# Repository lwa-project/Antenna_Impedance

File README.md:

Antenna_Impedance
===================

Description
-----------
Collection of scripts and files dealing with the LWA antenna impedance.

In the main directory are the general scripts:
* compute_IME.py: Reads in a single .s1p file containing antenna reflection coefficient data and computes the IME 
* plot_IME.py: Plots the output from computeIME.py along with the model IME from antenna simulations
* compute_IMF.py: Reads in a .npz file output by read_FEE_S_params.py and a collection of antenna .s2p files to compute the Impedance Mismatch Factor (IMF)
* plot_S_params.py: Takes in a collection of .s2p files and plots the full set of S-parameters for each antenna. Used to make the dipole-dipole measurement plots.
* plot_cross_coupling.py: Takes in a collection of .s2p files from an antenna-antenna cross coupling measurement and plots S12 and S21 for each of the four possible polarization permutations. 

Data Files
----------
In the Data/ directory there is a collection of various data files with their associated documentation.
Files include:
* BurnsZ.txt: Model IME from old antenna simulations
* A-NS_AntennaImpedance_062222.s1p: Antenna Impedance for A (N/S) polarization taken on 06/22/2022 at Whitham Reeve's house in Alaska
* B-EW_AntennaImpedance_062222.s1p: Antenna Impedance for B (E/W) polarization taken on 06/22/2022 at Whitham Reeve's house in Alaska
* A collection of dipole-dipole and antenna-antenna .s2p measurement files taken at the New Mexico stations (See "LWA_NM_Measurements_and_Procedures.pdf" for more information)

FEE
---
The Data/FEE/ directory contains:
* A collection of .s2p files which contains S-parameter measurements with the HX62A of the FEE Test Fixture de-embedded.
* read_FEE_S_params.py: A script to read both the .s1p and .s2p files and write out proper S-pramaters (S11 with HX62A de-embdedd, correct S21 and S12, and S22).
* plot_FEE_Gain.py: A script to plot the FEE Gain files which are output by read_FEE_S_params.py

Example
-------
The following is a short example which shows how to generate the IMF correction for LWA data, which requires both LWA antenna S11 measurements and FEE S11 measurements.
The FEE S11 data with the HX62A de-embedded are located in `Data/FEE/S1P/`. The single antenna measurements for each station are located in the named directories in the `Data/` directory
under `Dipole-Dipole/` (e.g. the LWA-SV measurements are in `Data/LWA-SV/Dipole-Dipole/`.

First, the FEE S-parameters with the HX62A de-embedded have to be collected into a single .npz file. To do this, use `Data/FEE/read_FEE_S_params.py` for both polarizations:
```
python3 read_FEE_S_params.py -ns S2P/*A*
```
and
```
python3 read_FEE_S_params.py -ns S2P/*B*
```
This creates two files `FEE_S11_NS.npz` and `FEE_S11_EW.npz`, respectively. Finally, to compute the IMF correction using LWA1 antenna measurements and FEE S11 measurements use `compute_IMF.py`
for each polarization via
```
python3 compute_IMF.py -ns Data/FEE/FEE_S11_NS.npz Data/LWA1/Dipole-Dipole/*
```
and
```
python3 compute_IMF.py -ns Data/FEE/FEE_S11_EW.npz Data/LWA1/Dipole-Dipole/*
```
This creates two files named `IMF_NS.txt` and `IMF_EW.txt`, respectively, which contain the IMF as a function of frequency along with the $16^{th}$ and $84^{th}$ percentile uncertainty bounds.

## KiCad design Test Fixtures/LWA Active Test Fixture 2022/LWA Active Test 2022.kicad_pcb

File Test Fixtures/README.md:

Test Fixtures
=============

Description
-----------
This directory contains the KiCAD v7 project files needed to build the test
fixtures used in [DiLullo et al. (2023, PASP)](https://arxiv.org/abs/2303.14904).
There are two sub-directories: "LWA Active Test Fixture 2022" and "LWA Cal Test
Fixture 2022".  "Active" contains the board that was used to make the impedance
measurements.  "Cal" contains the base board for making the open,
short, and load calibration fixtures for the measurements.

Within each sub-directory is the full KiCAD v7 project, the Gerber files, and BoM
for the board, relevant data sheets for the parts used, and an image of the
rendered 3D model of the full board.

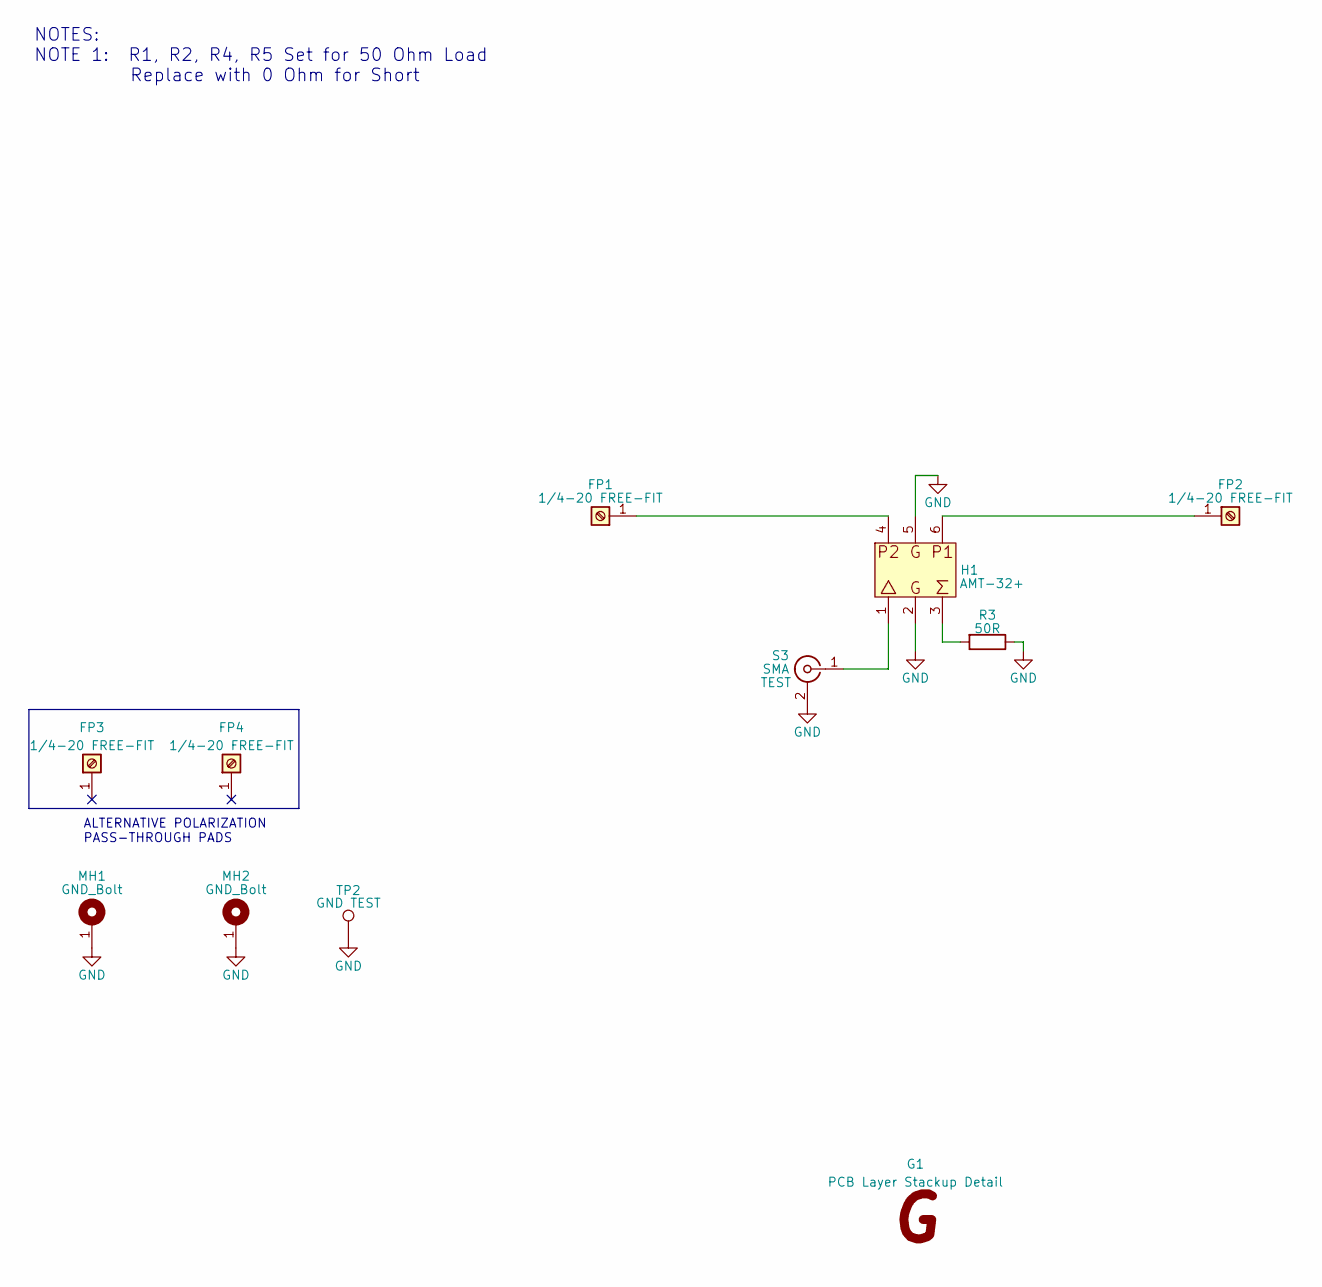
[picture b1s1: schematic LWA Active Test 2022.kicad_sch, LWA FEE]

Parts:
FP1, FP2, FP3, FP4: 1/4-20 FREE-FIT; Feedpoint; Tolerance NA; Voltage Rating NA; MPN DNI
G1: PCB Layer Stackup Detail; FabDrawing-2Layer-Imperial_LWA
H1: AMT-32+; AMT-2; Tolerance NA; Voltage Rating NA; MPN AMT-32+
MH1, MH2: GND_Bolt
R3: 50R; R_1206_3216Metric_Pad1.30x1.75mm_HandSolder; Tolerance 0.1%; Voltage Rating NA; MPN Y162550R0000B9W
S3: TEST; SMA_142-0701-201; Tolerance NA; Voltage Rating NA; MPN 142-0701-201
TP2: GND TEST; Harwin_TP_S1751-46R; Tolerance NA; Voltage Rating NA; MPN S1751-46R

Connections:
GND: H1.2, H1.5, MH1.1, MH2.1, R3.1, S3.2 (Ext), TP2.1
unnamed: FP1.1, H1.4
unnamed: H1.1, S3.1 (In)
unnamed: H1.3, R3.2
unnamed: FP2.1, H1.6

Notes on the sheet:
NOTES: NOTE 1: R1, R2, R4, R5 Set for 50 Ohm Load Replace with 0 Ohm for Short
ALTERNATIVE POLARIZATION PASS-THROUGH PADS

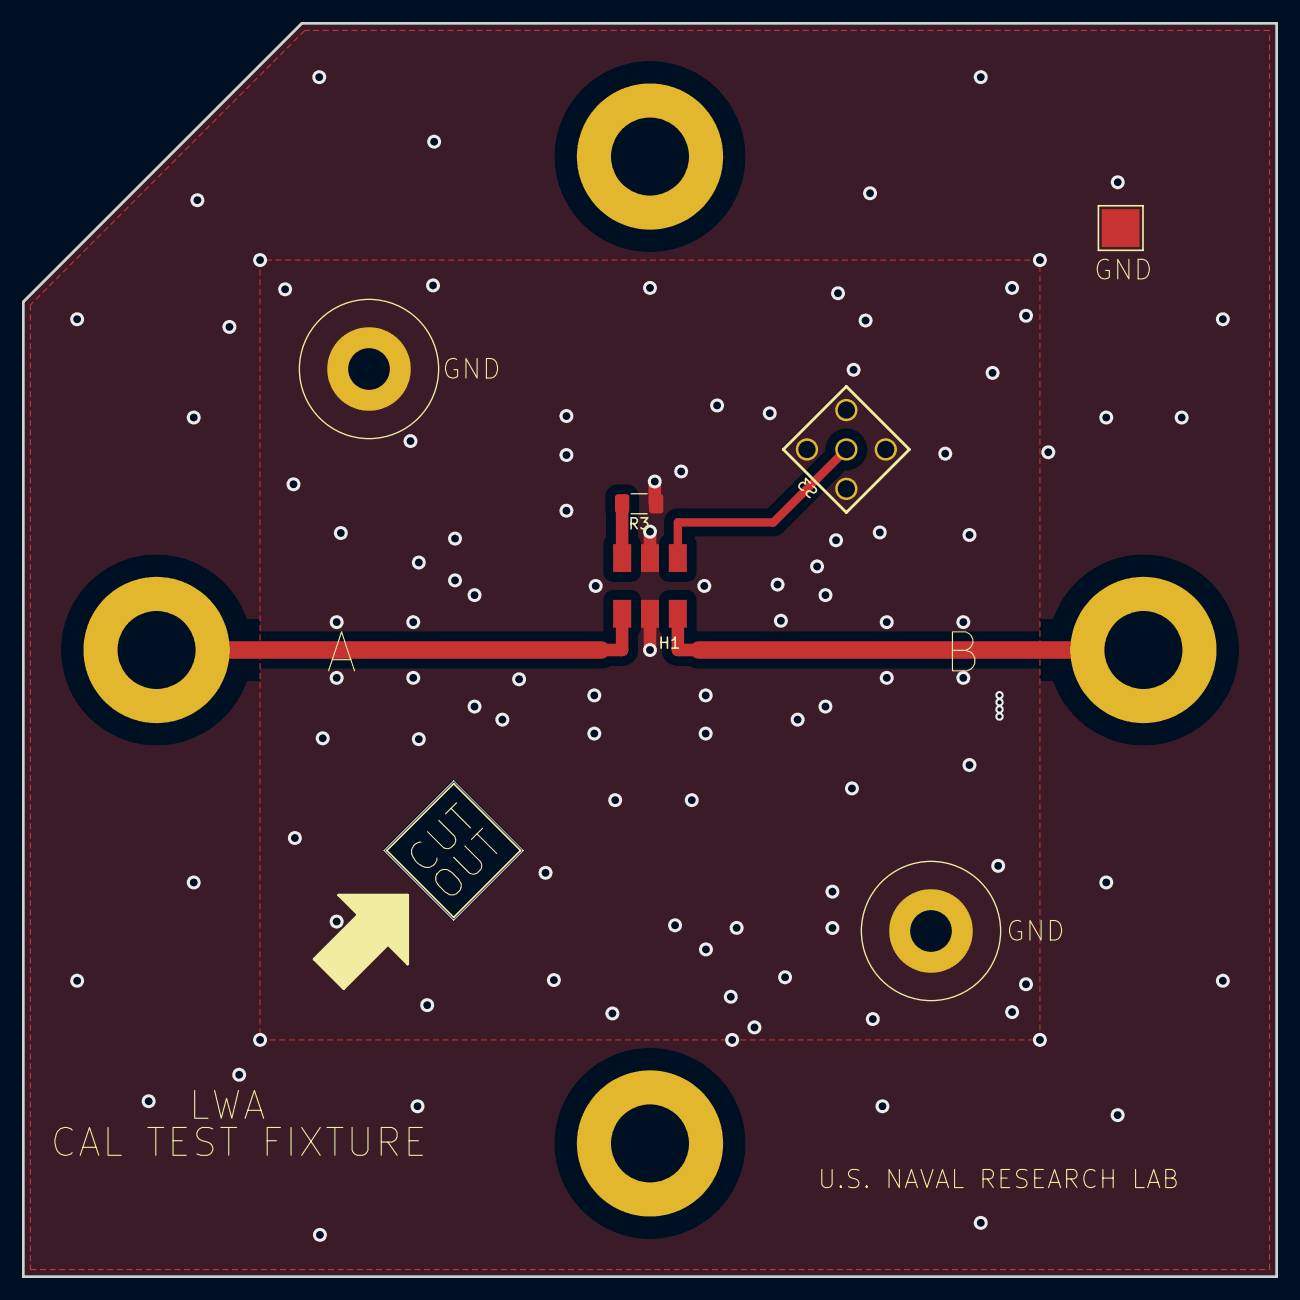
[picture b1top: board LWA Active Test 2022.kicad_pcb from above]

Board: 2 copper layers, 114.3 x 114.3 mm, 11 parts (1 on the bottom side), 5 nets.

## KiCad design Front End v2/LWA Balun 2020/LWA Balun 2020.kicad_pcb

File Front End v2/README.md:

LWA Front End Electronics (FEE) v2
==================================

Description
-----------
This directory contains the KiCAD v7 project files needed to build version 2 of
the LWA Front End Electronics board.  Inside "LWA Balun 2020" is the full KiCAD
v7 project, the Gerber files, and BoM for the board, relevant data sheets for
the parts used, and an image of the rendered 3D model of the full board.

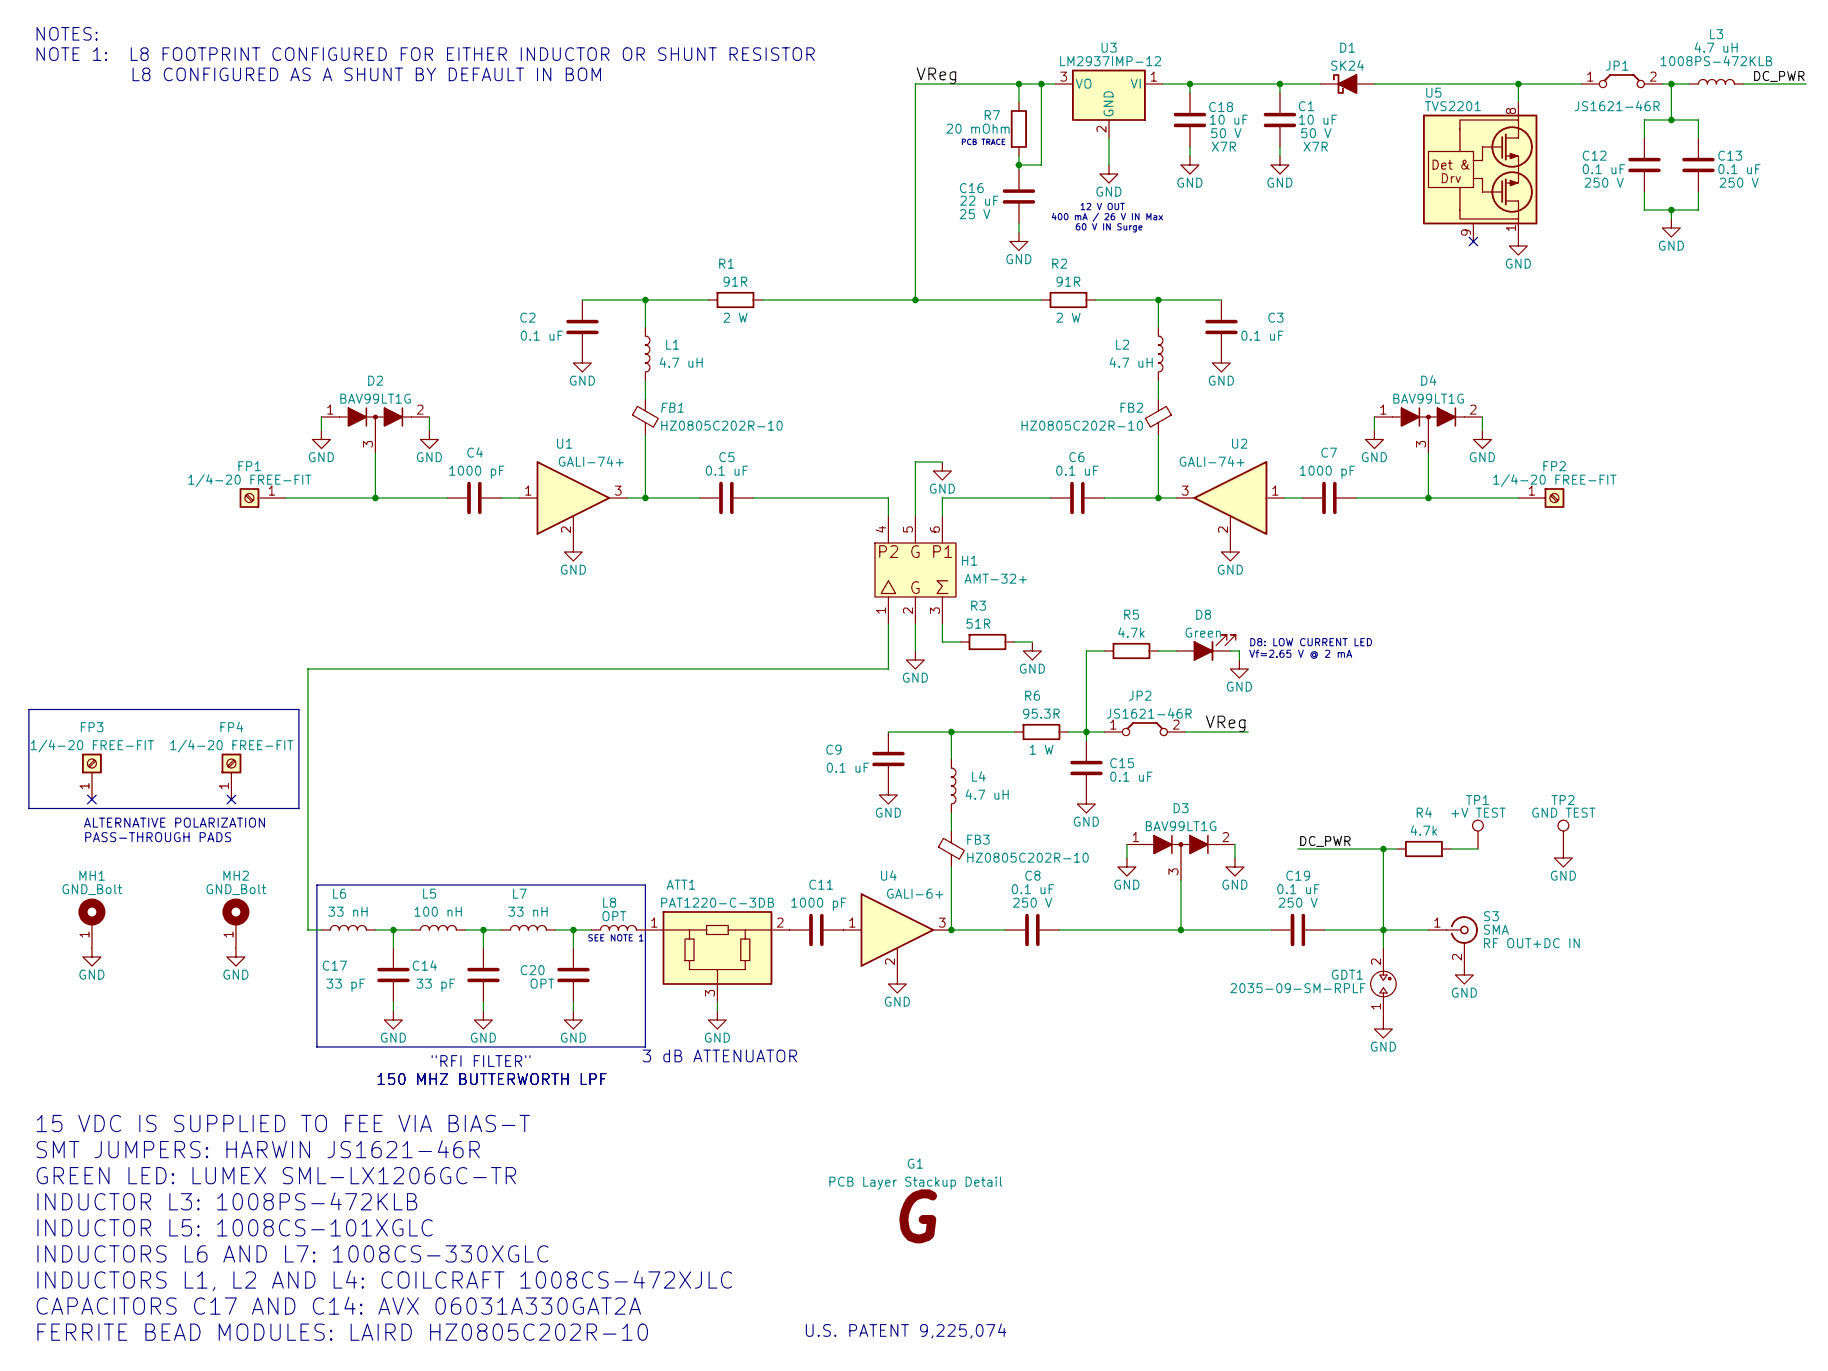
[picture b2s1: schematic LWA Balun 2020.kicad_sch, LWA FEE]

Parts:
ATT1: PAT1220-C-3DB; RF_Attenuator_Susumu_PAT1220_3D; Tolerance NA; Voltage Rating NA; MPN PAT1220-C-3DB-T5
C1, C18: 10 uF; C_1210_3225Metric_Pad1.33x2.70mm_HandSolder; Tolerance 10%; Voltage Rating 50 V; MPN CL32B106KBJNNWE
C2, C3, C5, C6, C8, C9, C12, C13, C15, C19: 0.1 uF; C_1206_3216Metric_Pad1.6x1.8mm; Tolerance 10%; Voltage Rating 250 V; MPN CC1206KKX7RYBB104
C4, C7, C11: 1000 pF; C_1206_3216Metric_Pad1.6x1.8mm; Tolerance 10%; Voltage Rating 630 V; MPN C1206C102KBRACTU
C14, C17: 33 pF; C_0603_1608Metric_Pad1.08x0.95mm_HandSolder; Tolerance 2%; Voltage Rating 100 V; MPN 06031A330GAT2A
C16: 22 uF; C_1210_3225Metric_Pad1.33x2.70mm_HandSolder; Tolerance 10%; Voltage Rating 25 V; MPN GRM32ER71E226ME15K
C20: OPT; C_0603_1608Metric_Pad1.08x0.95mm_HandSolder; Tolerance 2%; Voltage Rating 100 V; MPN DNI
D1: SK24; D_SMB_Handsoldering; Tolerance NA; Voltage Rating 500 mV @ 2 A; MPN SK24
D2, D3, D4: BAV99LT1G; SOT-23; Rating (A) 215 mA; Tolerance NA; MPN BAV99LT1G
D8: Green; LED_1206_3216Metric; Tolerance NA; Voltage Rating 2.65 V; MPN APT3216LZGCK
FB1, FB2, FB3: HZ0805C202R-10; L_0805_2012Metric_Pad1.15x1.40mm_HandSolder; Tolerance NA; Voltage Rating NA; MPN HZ0805C202R-10
FP1, FP2, FP3, FP4: 1/4-20 FREE-FIT; Feedpoint; Tolerance NA; Voltage Rating NA; MPN DNI
G1: PCB Layer Stackup Detail; FabDrawing-2Layer-Imperial_LWA
GDT1: 2035-09-SM-RPLF; Tolerance NA; Voltage Rating 90 V; MPN 2035-09-SM-RPLF
H1: AMT-32+; AMT-2; Tolerance NA; Voltage Rating NA; MPN AMT-32+
JP1, JP2: JS1621-46R; S1621-46R; Tolerance NA; Voltage Rating NA; MPN S1621-46R
L1, L2, L4: 4.7 uH; 1008CS; Tolerance 5%; Voltage Rating NA; MPN 1008CS-472XJLC
L3: 4.7 uH; 1008PS; Tolerance 10%; Voltage Rating NA; MPN 1008PS-472KLB
L5: 100 nH; 1008CS; Tolerance 2%; Voltage Rating NA; MPN 1008CS-101XGLC
L6, L7: 33 nH; 1008CS; Tolerance 2%; Voltage Rating NA; MPN 1008CS-330XGLC
L8: OPT; 1008CS_RES; Tolerance 2%; Voltage Rating NA; MPN RMCF0603ZT0R00
MH1, MH2: GND_Bolt
R1: 91R; R_2512_6332Metric_Pad1.8x3.35mm; Tolerance 1%; Voltage Rating NA; MPN 352191RFT
R2: 91R; R_2512_6332Metric_Pad1.8x3.35mm; Tolerance 1%; Voltage Rating 200 V; MPN 352191RFT
R3: 51R; R_1206_3216Metric_Pad1.30x1.75mm_HandSolder; Tolerance 1%; Voltage Rating NA; MPN RMCF1206FT51R0
R4, R5: 4.7k; R_1206_3216Metric_Pad1.30x1.75mm_HandSolder; Tolerance 5%; Voltage Rating NA; MPN ERJ-8GEYJ472V
R6: 95.3R; R_2512_6332Metric_Pad1.8x3.35mm; Tolerance 1%; Voltage Rating NA; MPN RMCF2512FT95R3
R7: 20 mOhm; ESR_20_mOhm; Tolerance NA; Voltage Rating NA; MPN Virtual
S3: RF OUT+DC IN; SMA_142-0701-201; Tolerance NA; Voltage Rating NA; MPN 142-0701-201
TP1: +V TEST; Harwin_TP_S1751-46R; Tolerance NA; Voltage Rating NA; MPN S1751-46R
TP2: GND TEST; Harwin_TP_S1751-46R; Tolerance NA; Voltage Rating NA; MPN S1751-46R
U1, U2: GALI-74+; MCL_Gali; Tolerance NA; Voltage Rating NA; MPN GALI-74+
U3: LM2937IMP-12; SOT-223-3_TabPin2; Tolerance NA; Voltage Rating NA; MPN LM2937IMP-12/NOPB
U4: GALI-6+; MCL_Gali; Tolerance NA; Voltage Rating NA; MPN GALI-6+
U5: TVS2201; Texas_DRB0008A_VSON-N8_No_Vias; Tolerance NA; Voltage Rating Standoff ±22 V / Clamping 29.6 V; MPN TVS2201DRBR

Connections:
/DC_PWR: C19.1, GDT1.2, L3.1, R4.1, S3.1 (In)
/VReg: C16.2, JP2.2 (B), R1.1, R2.1, R7.1, R7.2, U3.3 (VO)
GND: ATT1.3, C1.1, C2.1, C3.1, C9.1, C12.1, C13.1, C14.1, C15.1, C16.1, C17.1, C18.1, C20.1, D2.1 (K), D2.2 (A), D3.1 (K), D3.2 (A), D4.1 (K), D4.2 (A), D8.1 (K), GDT1.1, H1.2, H1.5, MH1.1, MH2.1, R3.1, S3.2 (Ext), TP2.1, U1.2, U2.2, U3.2 (GND), U4.2, U5.1 (GND), U5.2 (GND), U5.3 (GND), U5.4 (GND)
unnamed: ATT1.1, L8.2
unnamed: ATT1.2, C11.2
unnamed: C2.2, L1.1, R1.2
unnamed: C3.2, L2.1, R2.2
unnamed: C4.1, U1.1
unnamed: C5.1, H1.4
unnamed: C5.2, FB1.2, U1.3
unnamed: C6.1, H1.6
unnamed: C6.2, FB2.2, U2.3
unnamed: C7.1, U2.1
unnamed: C8.2, FB3.2, U4.3
unnamed: C9.2, L4.1, R6.2
unnamed: C11.1, U4.1
unnamed: C14.2, L5.2, L7.1
unnamed: C17.2, L5.1, L6.2
unnamed: C8.1, C19.2, D3.3 (K)
unnamed: C20.2, L7.2, L8.1
unnamed: D1.2 (A), JP1.1 (A), U5.5 (IN), U5.6 (IN), U5.7 (IN), U5.8 (IN)
unnamed: C1.2, C18.2, D1.1 (K), U3.1 (VI)
unnamed: D8.2 (A), R5.2
unnamed: FB1.1, L1.2
unnamed: FB2.1, L2.2
unnamed: FB3.1, L4.2
unnamed: C4.2, D2.3 (K), FP1.1
unnamed: C7.2, D4.3 (K), FP2.1
unnamed: H1.1, L6.1
unnamed: H1.3, R3.2
unnamed: C12.2, C13.2, JP1.2 (B), L3.2
unnamed: C15.2, JP2.1 (A), R5.1, R6.1
unnamed: R4.2, TP1.1

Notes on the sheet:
PCB TRACE
"RFI FILTER"
U.S. PATENT 9,225,074
150 MHZ BUTTERWORTH LPF
D8: LOW CURRENT LED Vf=2.65 V @ 2 mA
NOTES: NOTE 1: L8 FOOTPRINT CONFIGURED FOR EITHER INDUCTOR OR SHUNT RESISTOR L8 CONFIGURED AS A SHUNT BY DEFAULT IN BOM
SEE NOTE 1
3 dB ATTENUATOR
12 V OUT 400 mA / 26 V IN Max 60 V IN Surge
15 VDC IS SUPPLIED TO FEE VIA BIAS-T SMT JUMPERS: HARWIN JS1621-46R GREEN LED: LUMEX SML-LX1206GC-TR INDUCTOR L3: 1008PS-472KLB INDUCTOR L5: 1008CS-101XGLC INDUCTORS L6 AND L7: 1008CS-330XGLC INDUCTORS L1, L2 AND L4: COILCRAFT 1008CS-472XJLC CAPACITORS C17 AND C14: AVX 06031A330GAT2A FERRITE BEAD M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
ALTERNATIVE POLARIZATION PASS-THROUGH PADS

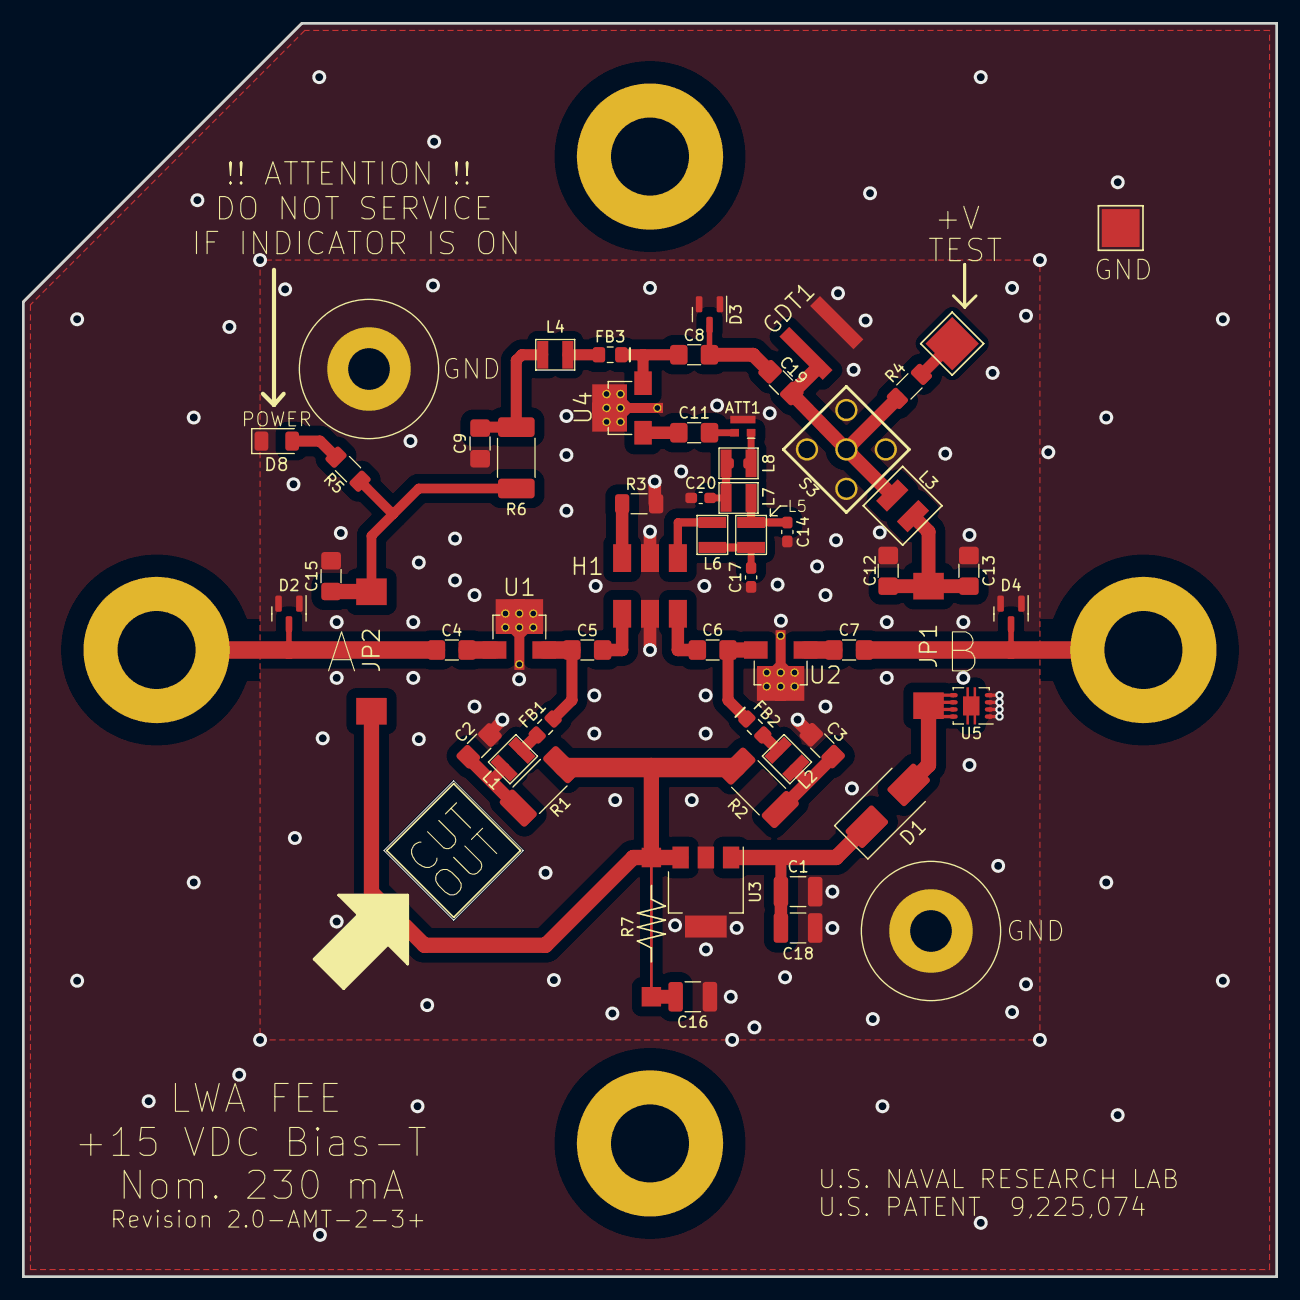
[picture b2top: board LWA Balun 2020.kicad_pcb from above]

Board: 2 copper layers, 114.3 x 114.3 mm, 62 parts (1 on the bottom side), 33 nets.

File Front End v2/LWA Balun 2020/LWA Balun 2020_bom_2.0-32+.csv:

Component,References,MFGR,MPN,Value,Desc,Footprint,Quantity Per PCB,Stock,Stock Date,Tolerance,Unit Cost
1,ATT1,Susumu,PAT1220-C-3DB-T5,PAT1220-C-3DB,RF ATTENUATOR 3DB 50OHM 0805,RF_Attenuator_Susumu_PAT1220_3D,1,80940,03/02/2022,NA,0.33
2,C14 C17,AVX,06031A330GAT2A,33 pF,CAP CER 33PF 100V C0G/NP0 0603,C_0603_1608Metric_Pad1.08x0.95mm_HandSolder,2,862,04/14/2022,2%,0.40
3,C4 C7 C11,KEMET,C1206C102KBRACTU,1000 pF,CAP CER 1000PF 630V X7R 1206,C_1206_3216Metric_Pad1.6x1.8mm,3,6278,03/02/2022,10%,0.32
4,C2 C3 C5 C6 C8 C9 C12 C13 C15 C19,Yageo,CC1206KKX7RYBB104,0.1 uF,CAP CER 0.1UF 250V X7R 1206,C_1206_3216Metric_Pad1.6x1.8mm,10,1075,03/02/2022,10%,0.33
5,C1 C18,Samsung,CL32B106KBJNNWE,10 uF,CAP CER 10UF 50V X7R 1210,C_1210_3225Metric_Pad1.33x2.70mm_HandSolder,2,15000,03/02/2022,10%,0.34
6,C16,KEMET,GRM32ER71E226ME15K,22 uF,CAP CER 22UF 25V X7R 1210,C_1210_3225Metric_Pad1.33x2.70mm_HandSolder,1,15270,03/02/2022,10%,1.25
7,C20 FP1 FP2 FP3 FP4,DNI,DNI,OPT,CAP CER TBD 0603 LWA FEE Feedpoint,C_0603_1608Metric_Pad1.08x0.95mm_HandSolder,5,TBD 1000,TBD 06/12/2020,2% NA,0.00
8,D2 D3 D4,ON Semiconductor,BAV99LT1G,BAV99LT1G,DIODE ARRAY 100V 215MA SOT23-3,SOT-23,3,8246,03/02/2022,NA,0.38
9,D8,Kingbright,APT3216LZGCK,Green,LED GREEN CLEAR 1206 SMD,LED_1206_3216Metric,1,44379,04/13/2022,NA,0.38
10,D1,Diotec Semiconductor,SK24,SK24,SCHOTTKY SMB 40V 2A,D_SMB_Handsoldering,1,2216850,03/03/2022,NA,0.07
11,FB1 FB2 FB3,Laird-Signal Integrity Products,HZ0805C202R-10,HZ0805C202R-10,FERRITE BEAD 2 KOHM 0805 1LN,L_0805_2012Metric_Pad1.15x1.40mm_HandSolder,3,180780,03/03/2022,NA,0.10
12,GDT1,Bourns Inc.,2035-09-SM-RPLF,2035-09-SM-RPLF,GDT 90V 5KA 2 POLE SURFACE MOUNT,2035-09-SM-RPLF,1,90060,03/03/2022,NA,0.64
13,H1,Mini-Circuits,AMT-32+,AMT-32+,"Magic Tee, 50 - 200 MHz, 180 deg Hybrid, 50Ω",AMT-2,1,66,03/03/2022,NA,13.45
14,JP1 JP2,Harwin Inc.,S1621-46R,JS1621-46R,JUMPER TIN SMD,S1621-46R,2,100419,03/03/2022,NA,0.15
15,L6 L7,Coilcraft,1008CS-330XGLC,33 nH,FIXED IND 1008 33nH 2% 1A 140mOhms,1008CS,2,3764,03/03/2022,2%,0.85
16,L5,Coilcraft,1008CS-101XGLC,100 nH,FIXED IND 1008 100nH 2% 650mA 560mOhms,1008CS,1,9701,03/03/2022,2%,0.85
17,L1 L2 L4,Coilcraft,1008CS-472XJLC,4.7 uH,FIXED IND 1008 4.7uH 5% 260mA 4Ohms,1008CS,3,77719,03/03/2022,5%,0.51
18,L3,Coilcraft,1008PS-472KLB,4.7 uH,FIXED IND 1008 4.7uH 5% 260mA 4Ohms,1008PS,1,9375,03/03/2022,10%,1.00
19,L8,Stackpole Electronics Inc,RMCF0603ZT0R00,OPT,RES 0 OHM JUMPER 1/10W 0603,1008CS_RES,1,5009095,03/03/2022,2%,0.01
20,R3,"Stackpole Electronics, Inc.",RMCF1206FT51R0,51R,RES 51 OHM 1% 1/4W 1206,R_1206_3216Metric_Pad1.30x1.75mm_HandSolder,1,57265,03/03/2022,1%,0.56
21,R1 R2,TE Connectivity Passive,352191RFT,91R,RES SMD 91 OHM 1% 2W 2512,R_2512_6332Metric_Pad1.8x3.35mm,2,6905,03/03/2022,1%,0.51
22,R6,Stackpole Electronics Inc,RMCF2512FT95R3,95.3R,RES 95.3 OHM 1% 1W 2512,R_2512_6332Metric_Pad1.8x3.35mm,1,11884,03/03/2022,1%,0.37
23,R4 R5,Panasonic Electronic Components,ERJ-8GEYJ472V,4.7k,RES SMD 4.7K OHM 5% 1/4W 1206,R_1206_3216Metric_Pad1.30x1.75mm_HandSolder,2,229032,03/03/2022,5%,0.05
24,S3,Cinch Connectivity Solutions Johnson,142-0701-201,RF OUT+DC IN,CONN SMA JACK STR 50 OHM PCB,SMA_142-0701-201,1,40347,03/03/2022,NA,4.94
25,TP1 TP2,Harwin Inc,S1751-46R,+V TEST,PC TEST POINT NATURAL,Harwin_TP_S1751-46R,2,157264,03/03/2022,NA,0.20
26,U4,Mini-Circuits,GALI-6+,GALI-6+,"SMT Low Noise Amplifier, DC - 4 GHz, 12.2 dB Gain, 4.5 dB NF, IP3O 35.5 dBm, 50Ω",MCL_Gali,1,650,03/03/2022,NA,1.65
27,U1 U2,Mini-Circuits,GALI-74+,GALI-74+,"SMT Low Noise Amplifier, DC - 1 GHz, 25.1 dB Gain, 2.7 dB NF, IP3O 38dBm, 50Ω",MCL_Gali,2,3424,03/03/2022,NA,2.65
28,U3,Texas Instruments,LM2937IMP-12/NOPB,LM2937IMP-12,IC REG LINEAR 12V 400MA SOT223-4,SOT-223-3_TabPin2,1,400,03/03/2022,NA,1.44
29,U5,Texas Instruments,TVS2201DRBR,TVS2201,IC BIIDIR FLAT CLAMP TVS,Texas_DRB0008A_VSON-N8_No_Vias,1,733,03/03/2022,NA,0.65





Component Groups:,29
Component Count:,58
Fitted Components:,58
Number of PCBs:,1
Total components:,58
Schematic Version:,2.0-32+
Schematic Date:,2022-04-13
PCB Variant:,default
BoM Date:,Thu 14 Apr 2022 01:18:13 PM EDT
Schematic Source:,LWA Balun 2020.kicad_sch
KiCad Version:,Eeschema 6.0.4-6f826c9f35~116~ubuntu20.04.1

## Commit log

2022-10-18 Added initial scripts
    These scripts are used to compute and plot the IME/IMF.
2022-10-18 Added data files
2022-10-18 Made scripts more robust and cleaned up file structure for the GitHub repo
2022-10-18 Made the scripts executable
2022-10-19 Included statistics for the other S parameters
2022-10-19 Removed some old code and added shading in IMF plot.
2022-11-15 Small cleaning edits to FEE_stats.py and addition of two scripts to plot S-parameters from the New Mexico trip.
2022-11-22 Small tweaks to read in .s2p files instead of .s1p. Also added the antenna data from the NM trip.
2022-11-22 Removed unneccesary print statement
2022-11-28 Restructured data directories. Made FEE_stats.py more robust about finding the proper polarizations to use when generating IMF
2022-12-13 Fixed how the antenna number is read from the file name
2022-12-13 Updated README and added some documentation about the NM measurements
2022-12-14 Better looking plots
2022-12-14 Added a .gitignore file
2022-12-21 Added option to plot the IME model on the IMF plot for paper purposes.
2023-01-03 Try using multiple antenna files to get better statistics on the IMF
2023-01-03 Cleaned up plot scales
2023-01-17 Renamed FEE_stats.py to compute_IMF.py. Also cleaned up how many files get saved.
2023-01-17 Changed FEE gain to voltage gain for consistency. Added convenience plotting script to quickly plot FEE gain.
2023-01-17 Forgot to make it executable
2023-01-20 Added HX62A S-parameter measurement data given by Whit in January 2023
2023-01-20 Updated the README to include info about the HX62A measurements and updated compute_IMF.py to read in the correction and apply it to the FEE Gain calculation
2023-01-21 Make `FEE_Gain_*.txt` consistent with its header
2023-01-21 Better data path handling
2023-01-21 Missing import
2023-01-21 Require at least one .s2p file
2023-01-21 Make sure we use only the filename, not the path
2023-01-21 Make sure we use only the filename, not the path - again
2023-01-21 More path and gain saving changes
2023-01-23 Renamed FEE data files and added .s1p support to compute_IMF.py
2023-01-23 Forgot to stage changes to comoute_IMF.py for commit
2023-01-23 Deleting files so I can reupload them.
2023-01-23 Uploaded the data files and include more documentation
2023-01-24 Just use HX62A S21 magnitude
2023-01-24 Made a plotting script that handles the FEE S-params
2023-01-24 Total overhaul on how FEE S-parameters are computed, plotted, and saved
2023-01-24 Cleanup and README update
2023-01-24 README cleanup
2023-01-31 Fixed weirdness with shaded error bounds on plots. Also set plot y-scales.
2023-02-13 Added an example on how to generate the IMF corrections to the README
2023-02-13 LaTex formatting
2023-02-13 Added links to Hicks et al. 2012 and LWA Memo #190
2023-02-13 Line break
2023-02-14 Switched documentation dection to badges at the top. This looks nicer.
2023-02-27 Fixed IMF plot percentile and changed read_FEE_S_params.py to just use .s2p files from the new FEE measurements
2023-02-28 Swapped FEE data files for Whit's new measurements. Fixed typo in read_FEE_S_params.py
2023-03-23 Removed HX62A data for clarity since we no longer use it in the analysis
2023-03-28 Added ArXiv reference to paper in the README
2023-05-06 Start with a README.md file.
2023-05-24 Added KiCAD files for the test/calibration fixtures and the v2 FEE board.
2023-05-24 Added a README.md.
2023-05-24 Another README.md file.
2023-05-25 Fixed typo in README references to paper. It was 2023, not 2021.
2023-06-09 The FEE now has its own repo.
2023-06-09 Add the FEE KiCAD files as a submodule.
2023-06-09 Update.
2023-06-09 Move KiBOM over to a submodule.
2023-06-09 Update to the KiBOM-as-submodule commit.
2023-06-09 Keep up with Front_End.
2023-06-09 Ignore HTML when determining what kind of repo this is.
2023-06-09 Try to get KiCAD in.
